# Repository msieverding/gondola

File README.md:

# gondola
## A parametric robot infrastructure for repeatable mobile experiments

This gondola was developed during a projet thesis at Graz University of Technology. This repository contains the following four main parts:
- Application Code for ESP8266 (/esp8266_controller)
- Printed circuit board (/esp8266_pcb)
- Some documentation and evaluation in .xls and .m files (/doc)
- 3D printed parts for this gondola (/3d_parts) copied from https://github.com/iprotonotarios/gondola

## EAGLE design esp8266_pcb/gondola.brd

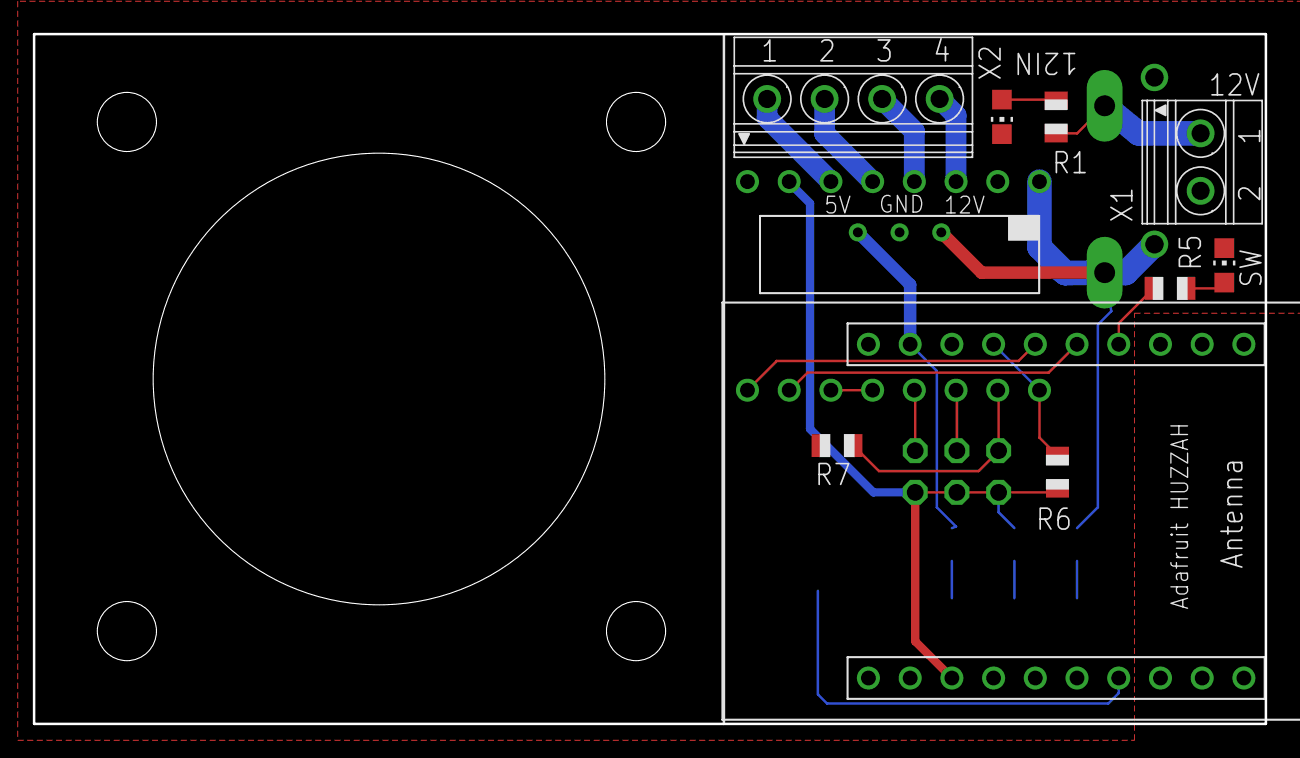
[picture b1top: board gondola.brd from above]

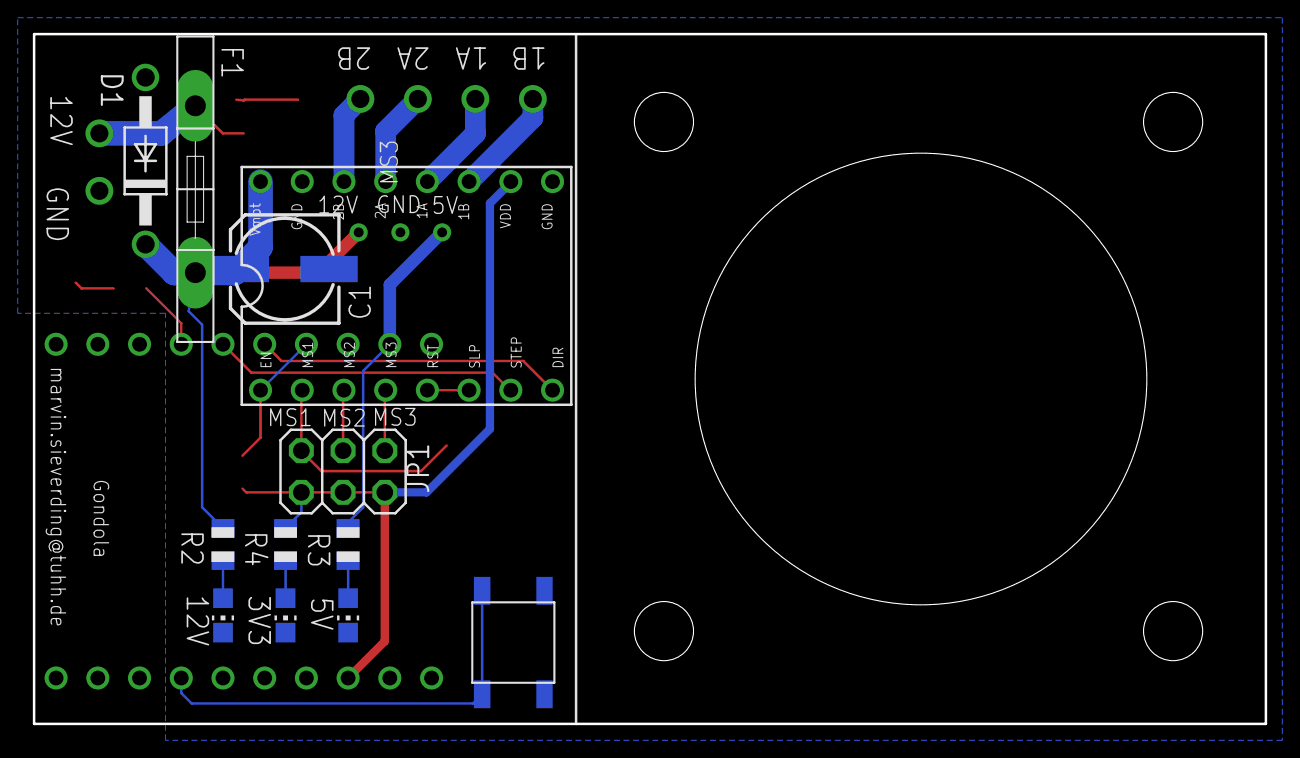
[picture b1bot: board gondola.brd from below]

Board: 2 copper layers, 75.0 x 42.0 mm, 22 parts (12 on the bottom side), 23 nets.

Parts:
C1: 100µF; 153CLV-0605
D1: 1N4004; DO41-10
F1: MFR500
JP1: 2X03
LED1_12IN, LED2_12V, LED3_5V, LED4_3V3, LED5_SW: CHIP-LED0805
R1, R2: 4.7k; R0805
R3: 1.2k; R0805
R4, R5: 330; R0805
R6, R7: 100k; R0805
U1: ROHM_BP5293-XX
U$1: A4988BREAKOUT
U$2: ADAFRUIT_ESP8266
U$4: FSMCTTR
X1: 1751248
X2: 1751264

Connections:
1A: U$1.1A, X2.2
1B: U$1.1B, X2.1
2A: U$1.2A, X2.3
2B: U$1.2B, X2.4
12V_IN: F1.P$1, R1.2, X1.1
!RESET: U$1.RST, U$1.SLP
+3V3: JP1.1, JP1.3, JP1.5, R4.2, R6.1, U$1.VDD, U$2.3_3V3
+5V: R3.2, U1.VOUT, U$2.9_VBAT
+12V: C1.+, D1.C, F1.P$2, R2.2, U1.VIN, U$1.VMOT
DIR: U$1.STEP, U$2.5_GPIO14
GND: C1.-, D1.A, LED1_12IN.C, LED2_12V.C, LED3_5V.C, LED4_3V3.C, LED5_SW.C, R7.2, U1.GND, U$1.GND, U$1.GND@0, U$2.1_GND, U$2.10_GND, U$4.1, U$4.2, X1.2
MS1: JP1.2, R7.1, U$1.MS1
MS2: JP1.4, U$1.MS2
MS3: JP1.6, U$1.MS3
M_EN: R6.2, U$1.EN, U$2.7_GPIO13
unnamed: LED2_12V.A, R2.1
unnamed: LED1_12IN.A, R1.1
unnamed: LED4_3V3.A, R4.1
unnamed: LED5_SW.A, R5.1
unnamed: LED3_5V.A, R3.1
STEP: U$1.DIR, U$2.6_GPIO12
SW_BUT: U$2.7_GPIO4, U$4.3, U$4.4
SW_LED: R5.2, U$2.4_GPIO16

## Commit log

2017-10-02 initial commit
    base repository: msieverding/gondola_arduino (forked from iprotonotarios/gondola)
    commit id: db645ba253deac1991805521f588c15f09427886
2017-10-02 add measurements and matlab evaluation
2017-10-02 updated BOM
2017-10-04 reduced log output
2017-10-04 added measurements from today and yesterday
2017-10-04 adjusted RemoteAnchor calculation to HardwareAnchorCalculation
2017-10-04 added ApplicationInterface
    Any appication can get the registerd gondola from here to set new position. So the application code isn't inside the gondola code
2017-10-04 added Error model for 2D and 3D with a given 1D Error
2017-10-05 Added seconds measurement to 2017_10_04_02 and added grid plots to the error models
2017-10-06 added RSSI application
2017-10-06 cherry picked some changes of the error model from the applicationRSSI branch
2017-10-06 changed input of error model to a coordinate
2017-10-06 Added estimated position for Anchors and Gondola. Additionally it's displayed on the web page
2017-10-09 updated readme's
2017-10-10 added Huzzah configuration and fixed connection issue with DualConnection
2017-10-10 added button to reset config and first implementation for RSSIApp
2017-10-11 some work on RSSI application
2017-10-11 some corrections in class diagram
2017-10-12 changes in matlab scripts for presentation
2017-10-16 added force
2017-10-16 added doxygen documentation
2017-10-17 changed maximum AP clients to
2017-10-17 workaround for bug in asynchronous mode
2017-10-17 some changes on the RSSI application
2017-10-17 adde second algorithm for RSSI Measurement
2017-10-27 deleted old layout. Corrected footbrint of button. Changed pins to Adafruit HUZZAH. Added RSSI measurements
2017-10-27 deleted and ignored temporary dia files
2017-11-03 added missing documentation and updated doxygen ouput
2017-11-16 changed violet colors in matlab diagrams. Updated class diagram
